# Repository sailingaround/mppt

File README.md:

# Mppt with rs485 status output
This is a small circuit providing an mppt power converter with these requirements:

 - up to 60v input
 - charge two lead-acid batteries (24V) (one should also be possible)
 - up to 4A current
 - rs485 status output for board computer

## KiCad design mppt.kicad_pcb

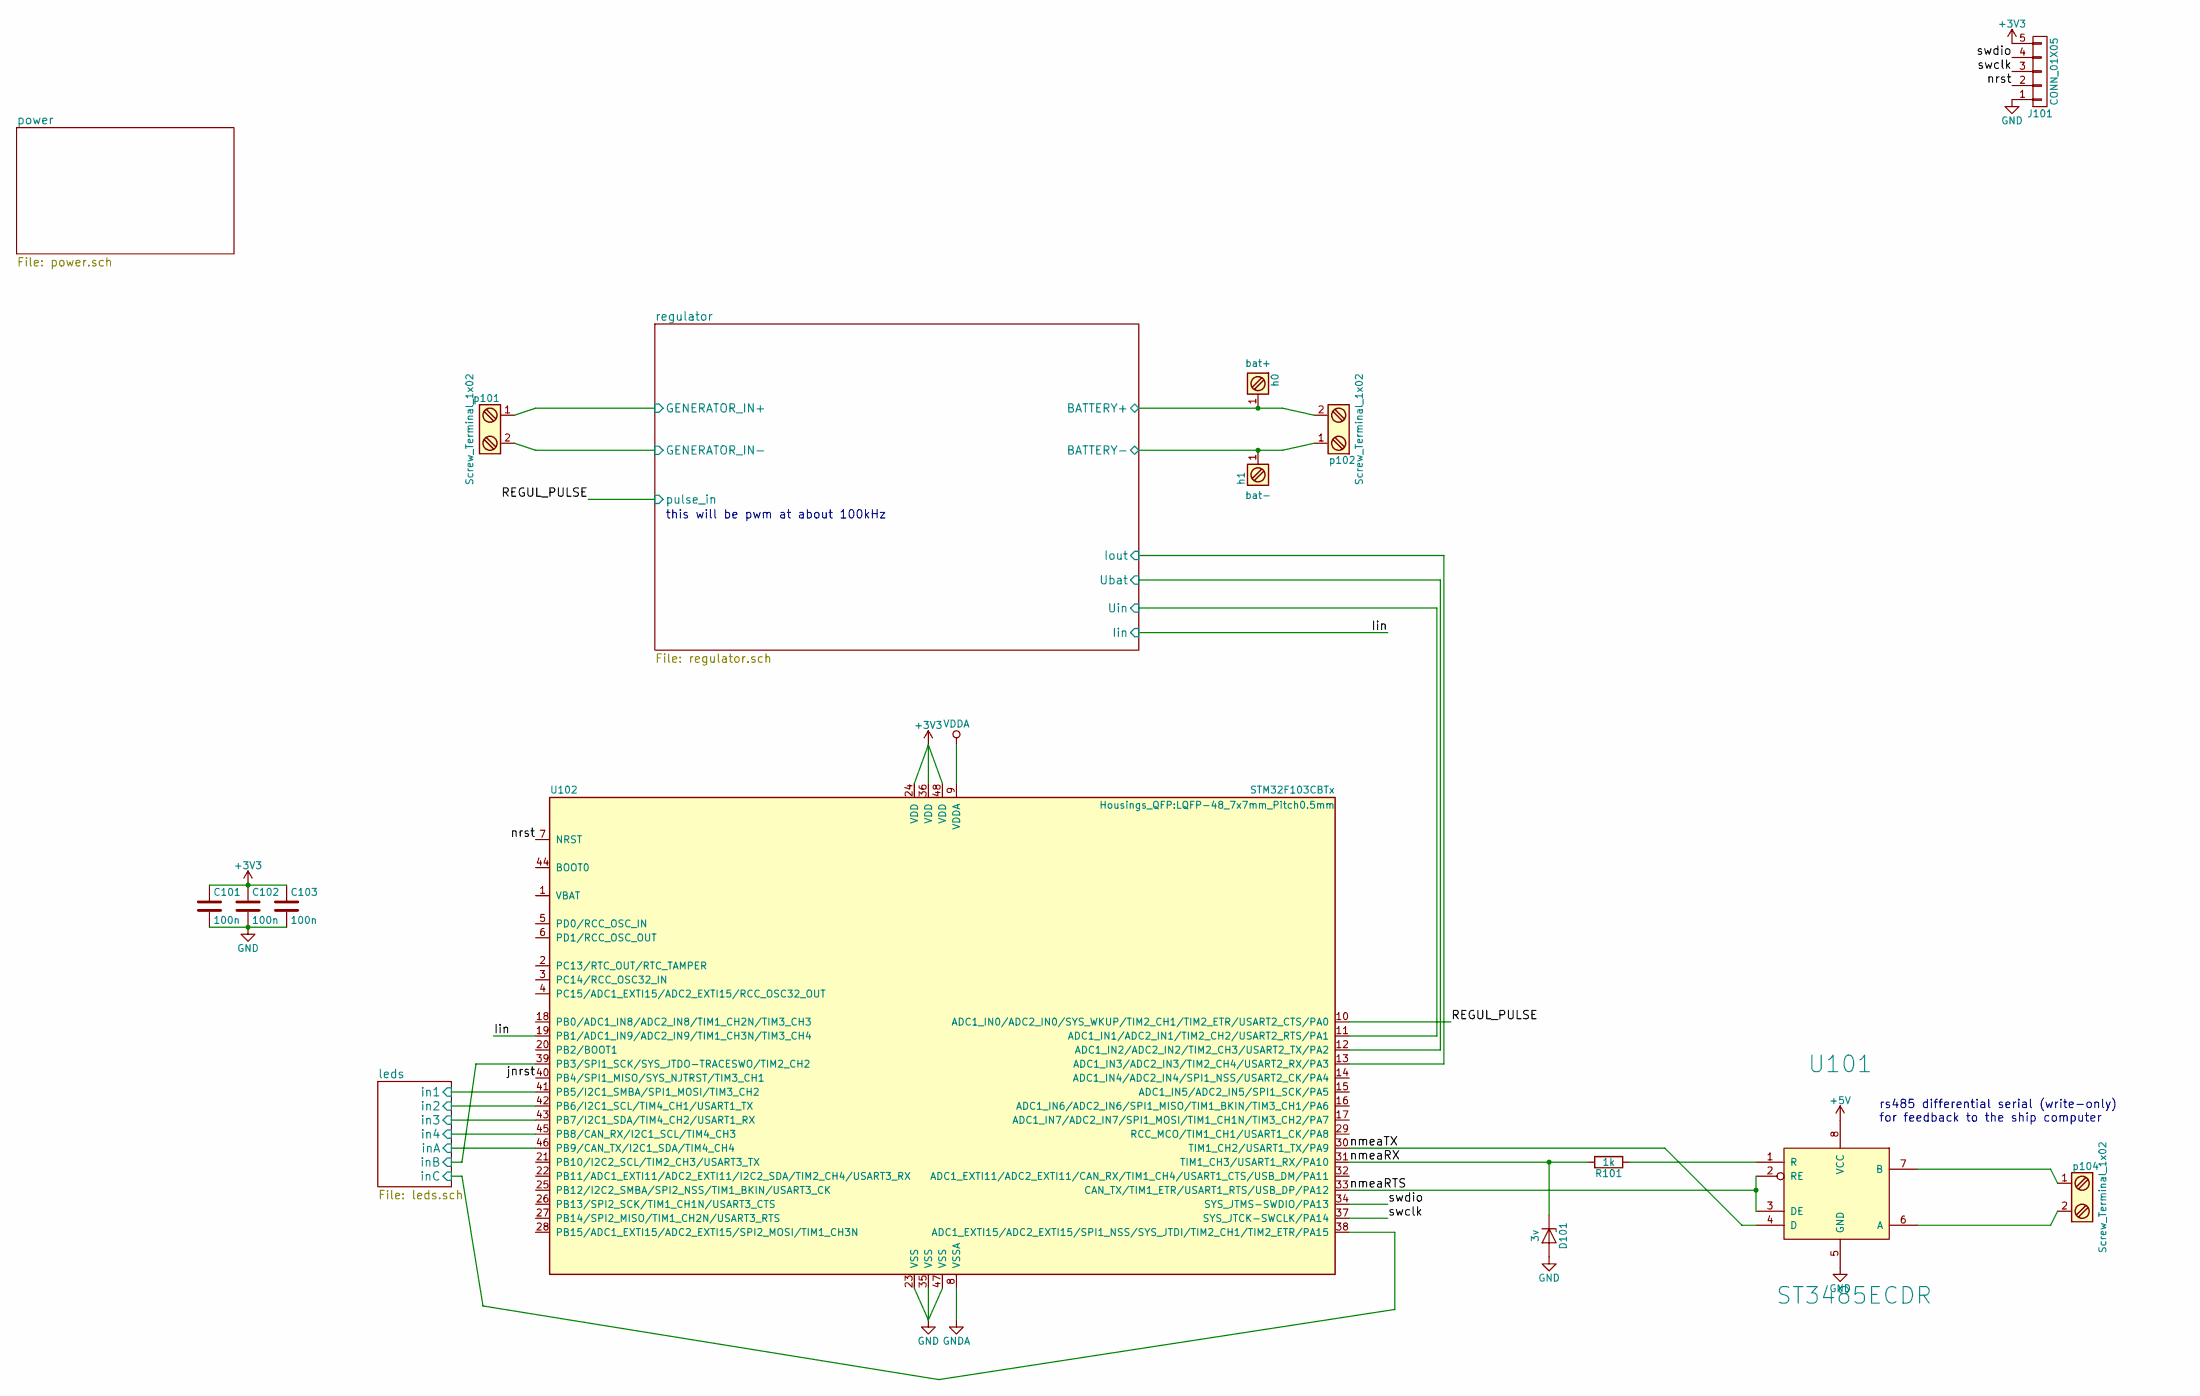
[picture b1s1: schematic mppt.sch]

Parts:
C101, C102, C103: 100n; C_0805
D101: 3v; D_SOD-323_HandSoldering; farnell 2441312
J101: CONN_01X05; swd_conn
R101: 1k; R_0805
U101: ST3485ECDR; SOIC-8_3.9x4.9mm_Pitch1.27mm; farnell 1842628
U102: STM32F103CBTx; LQFP-48_7x7mm_Pitch0.5mm
h0: bat+; m4_hole
h1: bat-; m4_hole
p101, p102, p104: Screw_Terminal_1x02; terminal

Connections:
+3V3: C101.1, C102.1, C103.1, J101.5, U102.24 (VDD), U102.36 (VDD), U102.48 (VDD); also elsewhere on the board
+5V: U101.8 (VCC); also elsewhere on the board
+24V: h0.1, p102.2; also elsewhere on the board
/Iin: U102.19 (PB1/ADC1_IN9/ADC2_IN9/TIM1_CH3N/TIM3_CH4); also elsewhere on the board
/REGUL_PULSE: U102.10 (ADC1_IN0/ADC2_IN0/SYS_WKUP/TIM2_CH1/TIM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); also elsewhere on the board
/leds/in1: U102.41 (PB5/I2C1_SMBA/SPI1_MOSI/TIM3_CH2); also elsewhere on the board
/leds/in2: U102.42 (PB6/I2C1_SCL/TIM4_CH1/USART1_TX); also elsewhere on the board
/leds/in3: U102.43 (PB7/I2C1_SDA/TIM4_CH2/USART1_RX); also elsewhere on the board
/leds/in4: U102.45 (PB8/CAN_RX/I2C1_SCL/TIM4_CH3); also elsewhere on the board
/leds/inA: U102.46 (PB9/CAN_TX/I2C1_SDA/TIM4_CH4); also elsewhere on the board
/leds/inB: U102.39 (PB3/SPI1_SCK/SYS_JTDO-TRACESWO/TIM2_CH2); also elsewhere on the board
/leds/inC: U102.38 (ADC1_EXTI15/ADC2_EXTI15/SPI1_NSS/SYS_JT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); also elsewhere on the board
/nmeaRTS: U101.2 (RE), U101.3 (DE), U102.33 (CAN_TX/TIM1_ETR/USART1_RTS/USB_DP/PA12)
/nmeaRX: D101.1 (K), R101.2, U102.31 (TIM1_CH3/USART1_RX/PA10)
/nmeaTX: U101.4 (D), U102.30 (TIM1_CH2/USART1_TX/PA9)
/nrst: J101.2, U102.7 (NRST)
/regulator/BATTERY-: h1.1, p102.1; also elsewhere on the board
/regulator/GENERATOR_IN+: p101.1; also elsewhere on the board
/regulator/GENERATOR_IN-: p101.2; also elsewhere on the board
/regulator/Iout: U102.13 (ADC1_IN3/ADC2_IN3/TIM2_CH4/USART2_RX/PA3); also elsewhere on the board
/regulator/Ubat: U102.12 (ADC1_IN2/ADC2_IN2/TIM2_CH3/USART2_TX/PA2); also elsewhere on the board
/regulator/Uin: U102.11 (ADC1_IN1/ADC2_IN1/TIM2_CH2/USART2_RTS/P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); also elsewhere on the board
/swclk: J101.3, U102.37 (SYS_JTCK-SWCLK/PA14)
/swdio: J101.4, U102.34 (SYS_JTMS-SWDIO/PA13)
GND: C101.2, C102.2, C103.2, D101.2 (A), J101.1, U101.5 (GND), U102.23 (VSS), U102.35 (VSS), U102.47 (VSS); also elsewhere on the board
GNDA: U102.8 (VSSA); also elsewhere on the board
unnamed: R101.1, U101.1 (R)
unnamed: U101.6 (A), p104.2
unnamed: U101.7 (B), p104.1
VDDA: U102.9 (VDDA); also elsewhere on the board

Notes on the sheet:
rs485 differential serial (write-only) for feedback to the ship computer
this will be pwm at about 100kHz

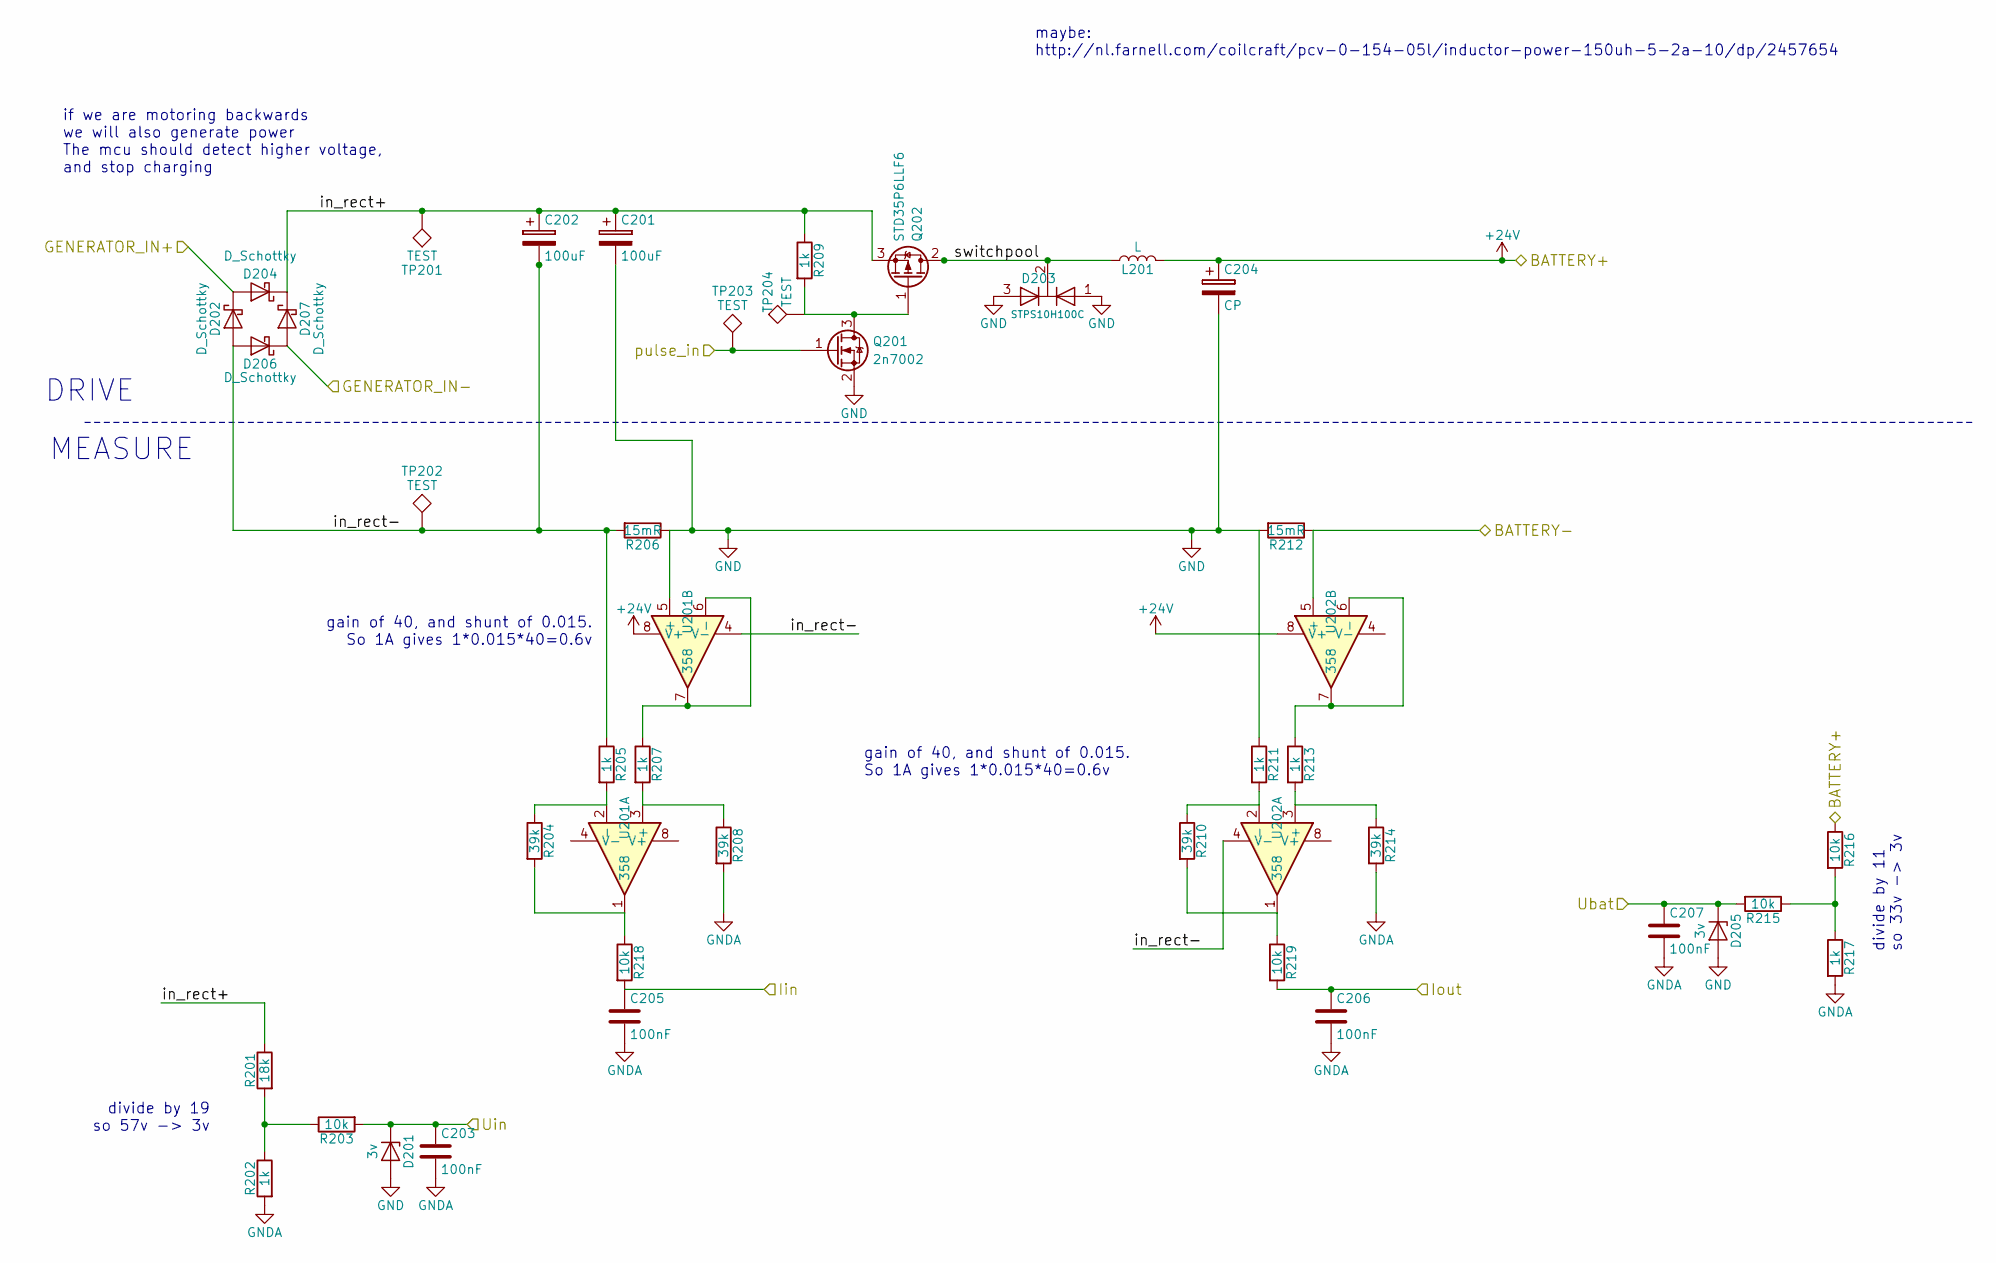
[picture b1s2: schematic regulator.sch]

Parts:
C201, C202: 100uF; CP_Radial_D10.0mm_P2.50mm; farnell 1281843
C203, C205, C206, C207: 100nF; C_0805
C204: CP; CP_Radial_D8.0mm_P5.00mm
D201, D205: 3v; D_SOD-323_HandSoldering; farnell 2441312
D202, D204, D206, D207: D_Schottky; Diode_DO-201AD_Vertical; farnell 1859669
D203: STPS10H100C; TO-220_Vertical
L201: L; toroid; farnell 1077015
Q201: 2n7002; SOT-23
Q202: STD35P6LLF6; TO-252-2Lead
R201: 18k; R_0805
R202, R205, R207, R209, R211, R213, R217: 1k; R_0805
R203, R215, R216, R218, R219: 10k; R_0805
R204, R208, R210, R214: 39k; R_0805
R206: 15mR; R_1206
R212: 15mR; R_1206_HandSoldering
TP201, TP202, TP203, TP204: TEST; Measurement_Point_Round-SMD-Pad_Big
U201, U202: 358; SOIC-8_3.9x4.9mm_Pitch1.27mm

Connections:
+24V: C204.1, L201.2, R216.1, U201.8 (V+), U202.8 (V+); also elsewhere on the board
/Iin: C205.1, R218.2; also elsewhere on the board
/REGUL_PULSE: Q201.1 (G), TP203.1; also elsewhere on the board
/regulator/BATTERY-: R212.1, U202.5 (+); also elsewhere on the board
/regulator/GENERATOR_IN+: D202.1 (K), D204.2 (A); also elsewhere on the board
/regulator/GENERATOR_IN-: D206.1 (K), D207.2 (A); also elsewhere on the board
/regulator/Iout: C206.1, R219.2; also elsewhere on the board
/regulator/Ubat: C207.1, D205.1 (K), R215.2; also elsewhere on the board
/regulator/Uin: C203.1, D201.1 (K), R203.2; also elsewhere on the board
/regulator/in_rect+: C201.1, C202.1, D204.1 (K), D207.1 (K), Q202.3 (S), R201.1, R209.1, TP201.1
/regulator/in_rect-: C202.2, D202.2 (A), D206.2 (A), R205.1, R206.2, TP202.1, U201.4 (V-), U202.4 (V-)
/regulator/switchpool: D203.2 (K), L201.1, Q202.2 (D)
GND: C201.2, C204.2, D201.2 (A), D203.1 (A), D203.3 (A), D205.2 (A), Q201.2 (S), R206.1, R211.1, R212.2, U201.5 (+); also elsewhere on the board
GNDA: C203.2, C205.2, C206.2, C207.2, R202.2, R208.2, R214.2, R217.2; also elsewhere on the board
unnamed: Q201.3 (D), Q202.1 (G), R209.2, TP204.1
unnamed: R201.2, R202.1, R203.1
unnamed: R204.1, R205.2, U201.2 (-)
unnamed: R204.2, R218.1, U201.1
unnamed: R207.1, U201.6 (-), U201.7
unnamed: R207.2, R208.1, U201.3 (+)
unnamed: R210.1, R211.2, U202.2 (-)
unnamed: R210.2, R219.1, U202.1
unnamed: R213.1, U202.6 (-), U202.7
unnamed: R213.2, R214.1, U202.3 (+)
unnamed: R215.1, R216.2, R217.1

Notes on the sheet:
divide by 19 so 57v -> 3v
if we are motoring backwards we will also generate power The mcu should detect higher voltage, and stop charging
divide by 11 so 33v -> 3v
DRIVE
MEASURE
gain of 40, and shunt of 0.015. So 1A gives 1*0.015*40=0.6v
maybe: http://nl.farnell.com/coilcraft/pcv-0-154-05l/inductor-power-150uh-5-2a-10/dp/2457654

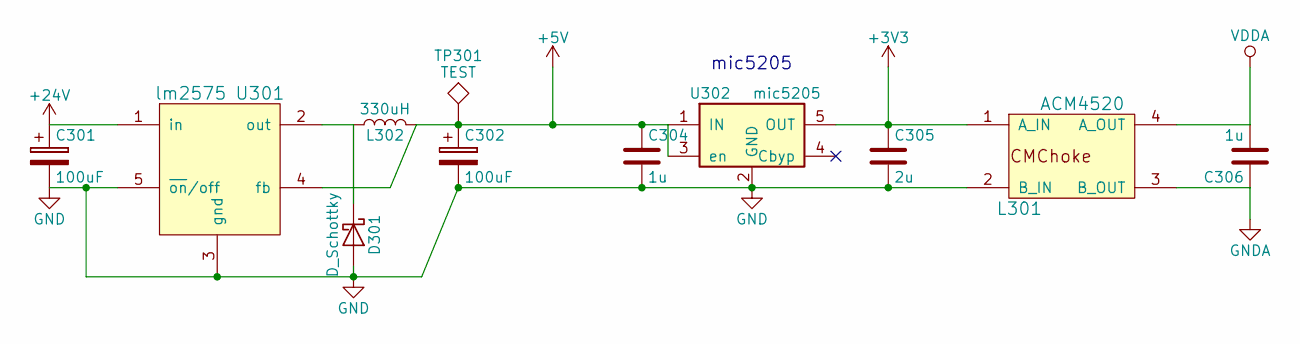
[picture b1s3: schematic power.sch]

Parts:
C301: 100uF; CP_Radial_D10.0mm_P2.50mm
C302: 100uF; CP_Radial_D8.0mm_P5.00mm
C304, C306: 1u; C_0805_HandSoldering
C305: 2u; C_0805_HandSoldering
D301: D_Schottky; D_DO-41_SOD81_P5.08mm_Vertical_KathodeUp
L301: ACM4520
L302: 330uH; 1212_inductor
TP301: TEST; Measurement_Point_Round-SMD-Pad_Big
U301: lm2575; TO-263-5Lead
U302: mic5205; SOT-23-5

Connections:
+3V3: C305.1, L301.1 (A_IN), U302.5 (OUT); also elsewhere on the board
+5V: C302.1, C304.1, L302.2, TP301.1, U301.4 (fb), U302.1 (IN), U302.3 (en); also elsewhere on the board
+24V: C301.1, U301.1 (in); also elsewhere on the board
GND: C301.2, C302.2, C304.2, C305.2, D301.2 (A), L301.2 (B_IN), U301.3 (gnd), U301.5 (~on~/off), U302.2 (GND); also elsewhere on the board
GNDA: C306.1, L301.3 (B_OUT); also elsewhere on the board
unnamed: D301.1 (K), L302.1, U301.2 (out)
VDDA: C306.2, L301.4 (A_OUT); also elsewhere on the board

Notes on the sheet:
mic5205

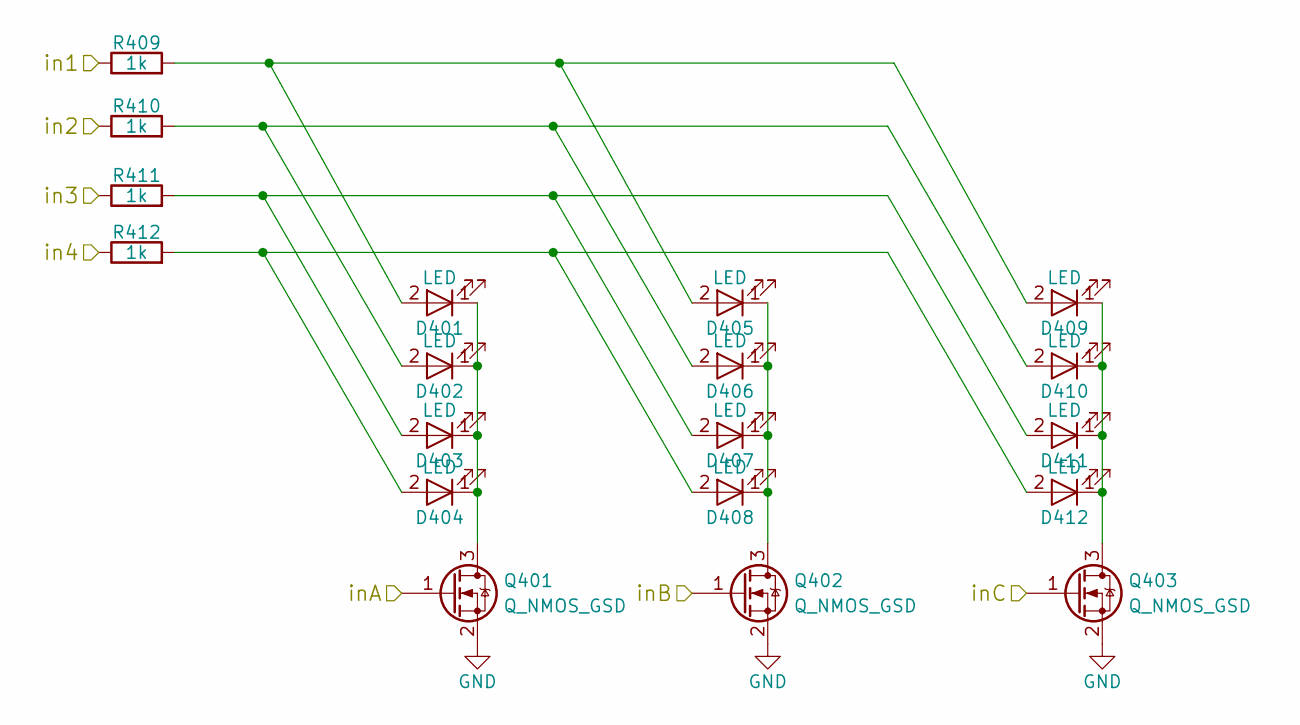
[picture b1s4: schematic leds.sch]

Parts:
D401, D402, D403, D404, D405, D406, D407, D408, D409, D410, D411, D412: LED; LED_0603
Q401, Q402, Q403: Q_NMOS_GSD; SOT-23_Handsoldering
R409, R410, R411, R412: 1k; R_0805

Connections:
/leds/in1: R409.1; also elsewhere on the board
/leds/in2: R410.1; also elsewhere on the board
/leds/in3: R411.1; also elsewhere on the board
/leds/in4: R412.1; also elsewhere on the board
/leds/inA: Q401.1 (G); also elsewhere on the board
/leds/inB: Q402.1 (G); also elsewhere on the board
/leds/inC: Q403.1 (G); also elsewhere on the board
GND: Q401.2 (S), Q402.2 (S), Q403.2 (S); also elsewhere on the board
unnamed: D401.1 (K), D402.1 (K), D403.1 (K), D404.1 (K), Q401.3 (D)
unnamed: D401.2 (A), D405.2 (A), D409.2 (A), R409.2
unnamed: D402.2 (A), D406.2 (A), D410.2 (A), R410.2
unnamed: D403.2 (A), D407.2 (A), D411.2 (A), R411.2
unnamed: D404.2 (A), D408.2 (A), D412.2 (A), R412.2
unnamed: D405.1 (K), D406.1 (K), D407.1 (K), D408.1 (K), Q402.3 (D)
unnamed: D409.1 (K), D410.1 (K), D411.1 (K), D412.1 (K), Q403.3 (D)

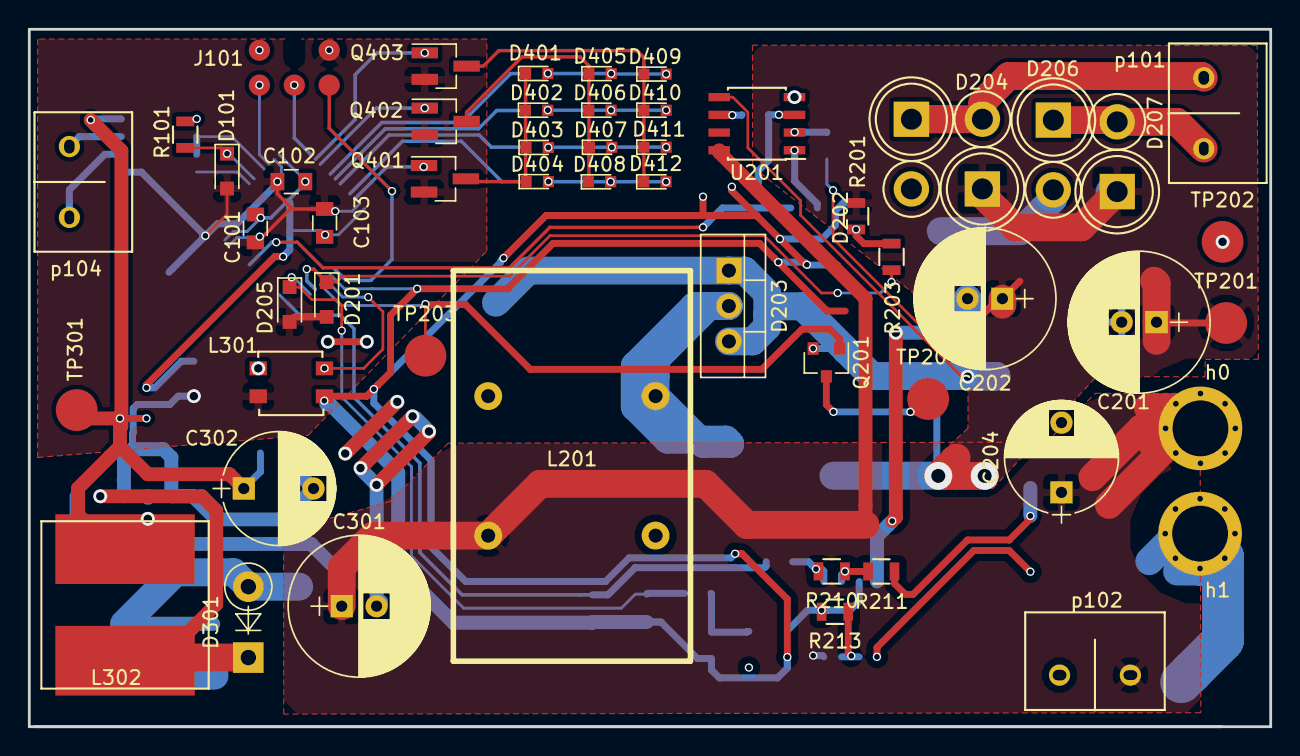
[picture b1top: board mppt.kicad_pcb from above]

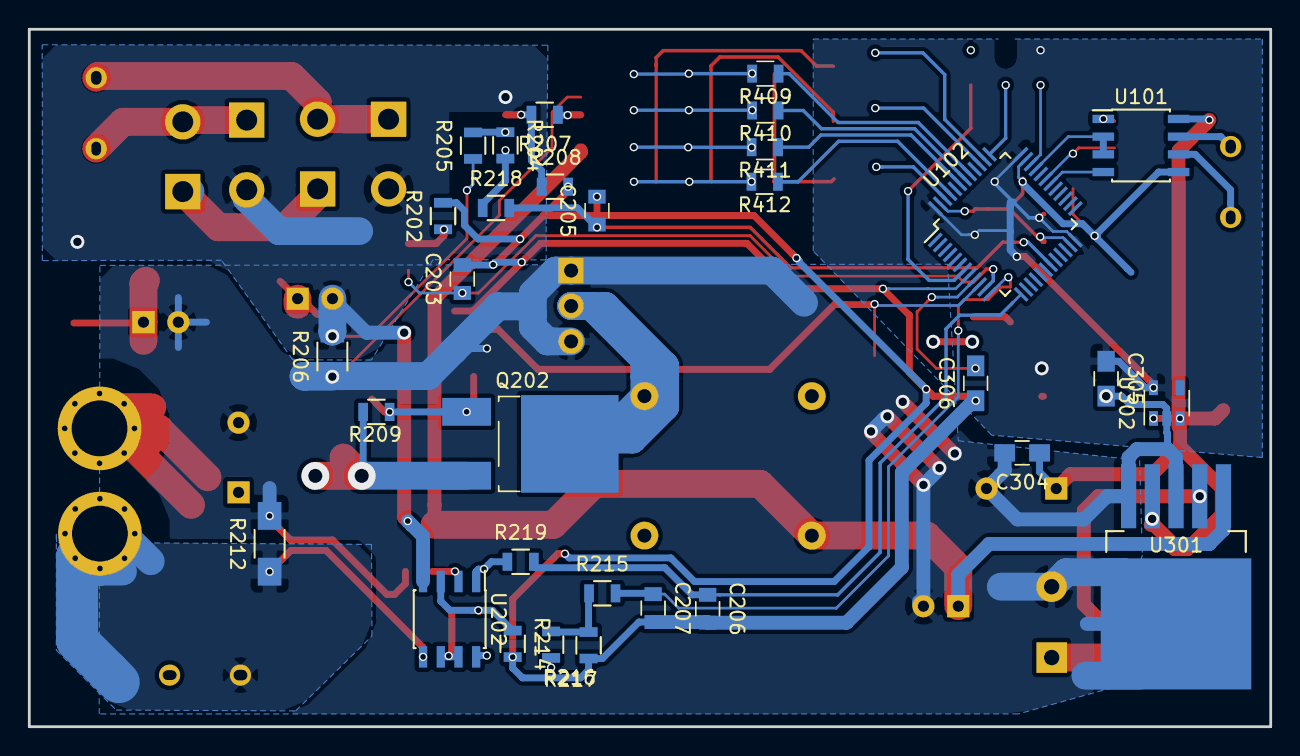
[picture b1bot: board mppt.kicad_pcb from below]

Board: 2 copper layers, 89.0 x 50.0 mm, 85 parts (31 on the bottom side), 52 nets.

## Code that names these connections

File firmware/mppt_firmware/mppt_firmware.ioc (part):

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Mcu.Name=STM32F103C(8-B)Tx
Mcu.Package=LQFP48
Mcu.UserName=STM32F103C8Tx
PA1.Signal=ADCx_IN1
PA10.Mode=Asynchronous
PA10.Signal=USART1_RX
PA12.Mode=RTS_Only
PA12.Signal=USART1_RTS
PA13.Mode=Serial_Wire
PA13.Signal=SYS_JTMS-SWDIO
PA14.Mode=Serial_Wire
PA14.Signal=SYS_JTCK-SWCLK
PA2.Signal=ADCx_IN2
PA3.Signal=ADCx_IN3
PA9.Mode=Asynchronous
PA9.Signal=USART1_TX
PB0.Signal=ADCx_IN8
PB1.Signal=ADCx_IN9
PB5.GPIOParameters=GPIO_Label
PB5.GPIO_Label=led_red
PB5.Signal=GPIO_Output
PB6.GPIOParameters=GPIO_Label
PB6.GPIO_Label=led_green
PB6.Signal=GPIO_Input
RCC.SYSCLKFreq_VALUE=32000000
RCC.SYSCLKSource=RCC_SYSCLKSOURCE_PLLCLK
board=mppt_firmware

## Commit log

2016-12-18 added firmware stub with cubemx file
2016-12-24 Added inital version of the hardware.
2016-12-25 Changed a bit, and did a full re-route
2017-01-30 Routed for 5x5 pcb
2017-02-28 Rerouted, and made everything beautifull
    - added screw bolt-holes for the output.
2017-03-02 Added small display.
    And made everything look even nicer
